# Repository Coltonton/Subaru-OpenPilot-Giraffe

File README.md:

# Subaru-OpenPilot-Giraffe(s) 

Here lies the olden and golden days of OpenPilot with Giraffes! You can use this product to interface with the CAN bus on your Subaru vehicle at EyeSight, giving the bonus ability to isolate the EyeSight module on its own separate CAN network for vehicle research, and hacking. 

Some of the Giraffes have mistakes, everything in the `/Legacy Archival Giraffes` folder is just that, a digital archive of most of my work. Most of the "development" Giraffes are lost to time and poor archival management, but live in the release of that version. DO NOT use these files as reference to build your own. ONLY use Austin, Cynthia, or Linda. 

- Intended to be used with a [Comma.ai White or Grey Panda](https://comma.ai/shop/products/panda) 

# Versions  
## -V3- 

3.0 Was the real move and evolution, finally fitting it in the cover (Also what the **Smol Bugsy Giraffe** tried to accomplish but in a different way.) I decided to stick on this path for a variety of reasons! I figured out there was no room under the cover... HOWEVER there was tons of room between the top of the EyeSight unit and the roof of the car. I already basically figured it out tho with [V1.1](#). Sometimes you have to look to the past to answer questions today! Again I was over-Zellous with V1.1; but with sure luck, the space allotted to me by the Subaru engineers was a near perfect fit for Panda... Not even a MM of clearance at the smallest point. Working even more perfectly. So is born V3! Only taking to V3 Rev 4 (NIKI) to come up with the perfect and final layout; even solving my switch problem by making the board big enough to where the switches would just be at the gap between the windshield and trim piece. giving a still invisible appearance, but not to difficult to actuate! Progress was made here!  

The V3 also brought reverse compatibility with already dead hardware (The Comma NEO) And was designed to have the factory connector pass above the EyeSight camera unit, plug into giraffe, then having a jumper connector to EyeSight. This ended up only being a possibility for the Legacy/Outback models. All other Subarus did not have the room for the chonky stock connector. Sparking V3.7+ with its Y connector to pass above the camera unit. (I still prefer the Linda design, was nicer and ALOT easier to produce....) 

### -V3.8.3 Austin- 

This is a very special edition of the Subaru Giraffe, not only is it the last version to be released; but it was sold as special edition Giraffe. Released in a special blue PCB and dedicated to the memory of my friend and classmate from grade school, Austin, who was tragically taken from us March 20th, 2019; at the too young age of 19. Until we meet again... 

This revision is still very near and dear to my heart and it pained me to no longer use it in my vehicle daily being forced to upgrade to a Black Panda, it's now on my desk where I get to see it daily. But enough with the wishy-washy crap and onto the info! As you can prolly tell by the x.x.3 i screwed this revision up.... a-couple times.... 

- The DeFacto Standard, this is what you should use! 

- Is the "gloabal platform" release Giraffe for use in all Subarus, whereas all previous V3 Giraffes were designed around a 2015 Legacy (and has a lot more room to play) 

- Replaced the 3.7 Cynthia as this version was a 3.7 special edition! But its the same thing 

### -V3.7 Cynthia- 

- First iteration of the Subaru global support 

- See [Austin](#V3.8.3-Austin) for details, they are the same, [Austin](#V3.8.3-Austin) is just a special edition of Cynthia with more beautiful routing! 

### -V3.6 Linda- 

- 2015-2019 Legacy/Outback Only 
- Added Subaru RAB Support 
- Added New Comma (Camera on CAN 3 instead of 2) Support 

### -V3.4 Niki- 

- 2015-2019 Legacy/Outback Only 
- Non RAB (Reverse Automatic Braking) Subarus ONLY 

### -V3.2 & V3.3 Gem- 

- 2015-2019 Legacy/Outback Only 
- Non RAB (Reverse Automatic Braking) Subarus ONLY 

### -V3.1 VIKI- 

- What Autum was supposed to be 

### -V3.0 Autumn- 
Dedicated to the memory of a co-worker who died unexpectedly, Autumn, to launch the 3rd generation of Subaru Giraffes (Non Working) 

## -V2- 

2.0 is a perfect example of my mind thinking more complex at first then working to simplicity. The idea with this weird Giraffe was to be like all the other Giraffes at the time where the board plugs directly into the cameras and the factory harness plugs into the board. This was a stupid idea as it would require cutting the EyeSight cover (or having it off) Witch we already had agreed was not going to happen... Too ugly, and expensive. It made a great development board as we were still trying to get the Subaru port "functional" It even uses the exact dip switches as the others. But with a twist... My overengineering mind went crazy with ideas as I knew the Giraffe would end up getting hidden up in the cover; I still wanted an easy way to have the traditional "switches" to be able to toggle Stock/Openpilot. What did I do? the only logical thing of course relays that could be hooked up to a switch and ran! It was a development platform so the *idea* was to be able to choose between dip switches or relay. I'm pretty sure they wouldn't work anyway as they are Solid state relays... idk... never tried them... 

It's funny because a year later Comma.ai made the **Subaru Access Point** with... a relay..... to control switching.... Eventually becoming the [Comma Harnes](https://comma.ai/shop/products/comma-car-harness)....  Admittedly they did do it better.... Except for using the USB Type-C Connectors...... It would of been the eventual evolution of my product to go back to relay control anyway! I take one big leap, have to crawl backwards crying and work my way back.....   

## -V1- 

Mr Overthinkers, first Giraffe overthink, before I found out Panda did fit somewhere in the EyeSight cover I had the brilliant idea to tear apart the Comma Panda and just put it on the Giraffe 

Rip White Panda - unknown year 

Features Eletronic relays that could be used to solve our switch situation (im writing this in reverse order so see V2 for info on that....) 

## -V0.1- 

**My First PCB** features include: 
- 90deg track corners 
- Weird angle lines (non 45deg multiple) 
- OBD socket doesn't even fit 
- Eyesight connectors don't even fit 
- No idea what I was doing (clearly) 
- Absolute trash 
- Prolly will blow up your car

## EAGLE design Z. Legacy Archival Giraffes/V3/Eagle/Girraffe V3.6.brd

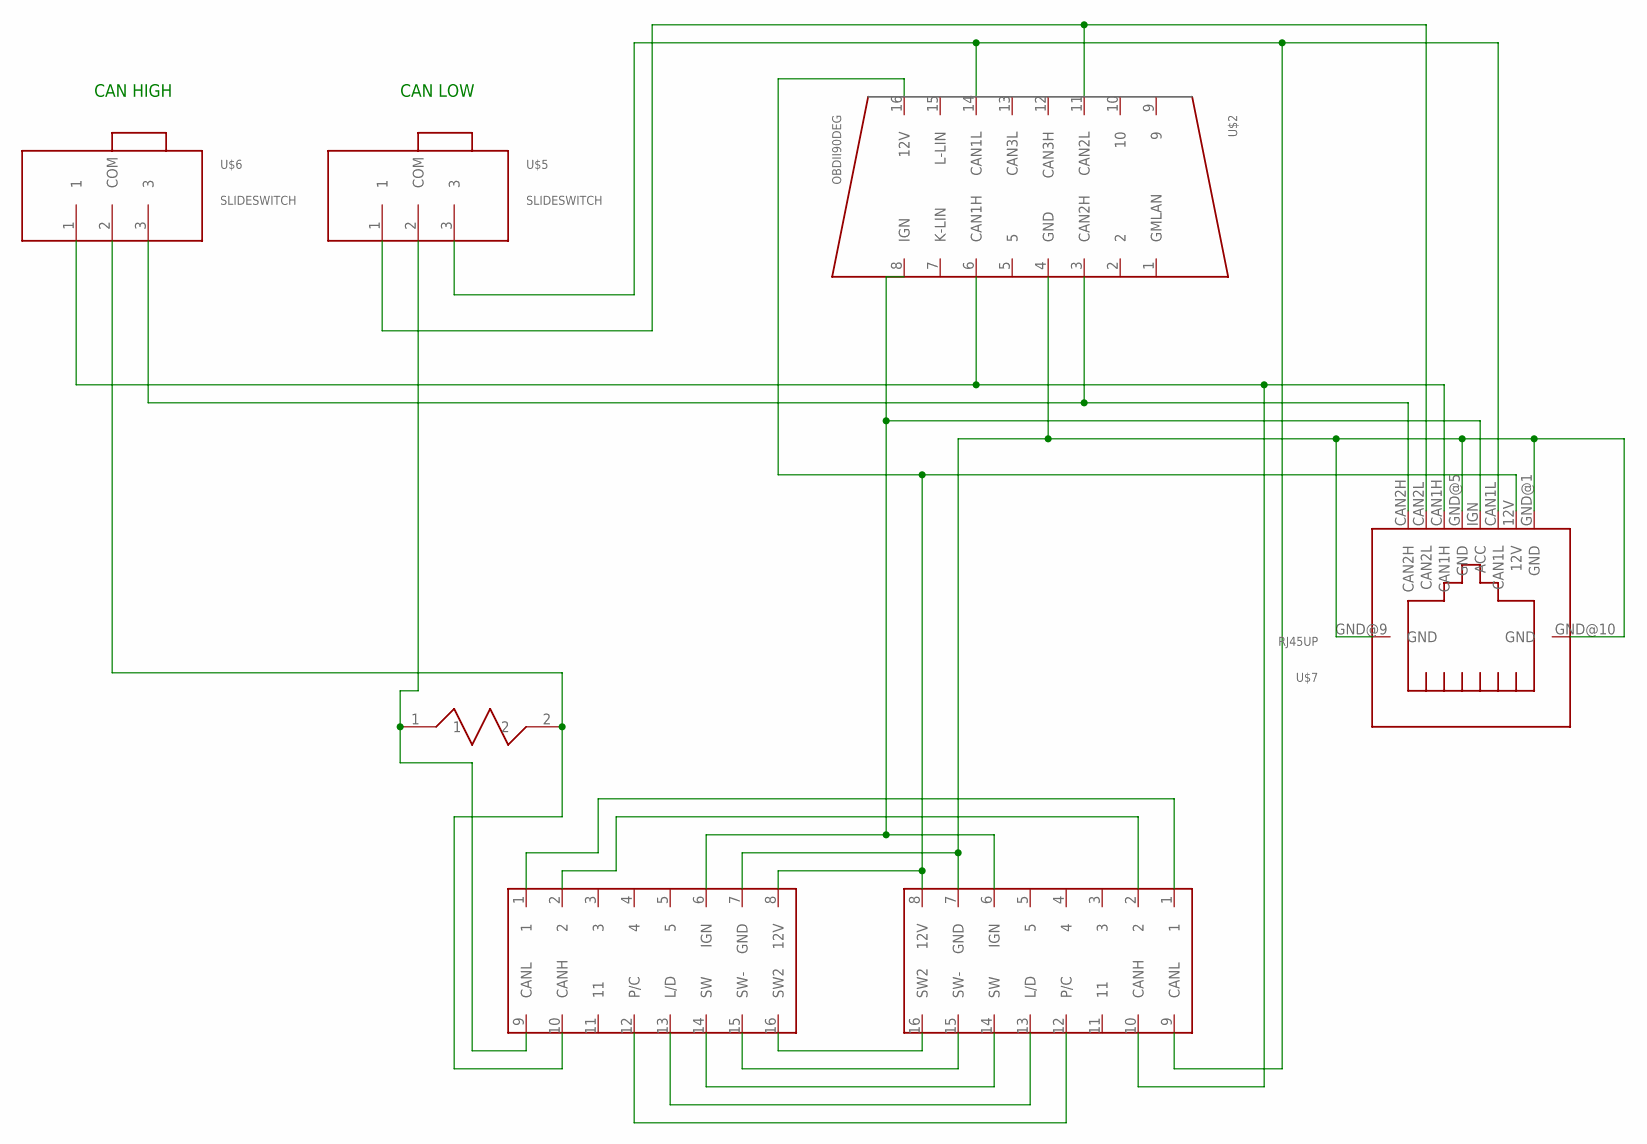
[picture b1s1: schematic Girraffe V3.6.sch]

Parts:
U$1: 120OHM
U$2: OBDII90DEG; OBDII
U$3: R137IN; R137
U$4: R137OUT
U$5, U$6: SLIDESWITCH
U$7: RJ45UP; VERRJ45

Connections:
12V: U$2.16 (12V), U$3.8 (12V), U$4.8 (12V), U$7.12V
ACC: U$2.8 (IGN), U$3.6 (IGN), U$4.6 (IGN), U$7.IGN (ACC)
GND: U$2.4 (GND), U$3.7 (GND), U$4.7 (GND), U$7.GND@1 (GND), U$7.GND@5 (GND), U$7.GND@9 (GND), U$7.GND@10 (GND)
unnamed: U$1.1, U$4.9 (CANL), U$5.2 (COM)
unnamed: U$1.2, U$4.10 (CANH), U$6.2 (COM)
unnamed: U$2.14 (CAN1L), U$3.9 (CANL), U$5.3, U$7.CAN1L
unnamed: U$2.11 (CAN2L), U$5.1, U$7.CAN2L
unnamed: U$2.6 (CAN1H), U$3.10 (CANH), U$6.1, U$7.CAN1H
unnamed: U$2.3 (CAN2H), U$6.3, U$7.CAN2H
unnamed: U$3.16 (SW2), U$4.16 (SW2)
unnamed: U$3.15 (SW-), U$4.15 (SW-)
unnamed: U$3.14 (SW), U$4.14 (SW)
unnamed: U$3.13 (L/D), U$4.13 (L/D)
unnamed: U$3.12 (P/C), U$4.12 (P/C)
unnamed: U$3.2, U$4.2
unnamed: U$3.1, U$4.1

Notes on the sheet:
CAN LOW
CAN HIGH

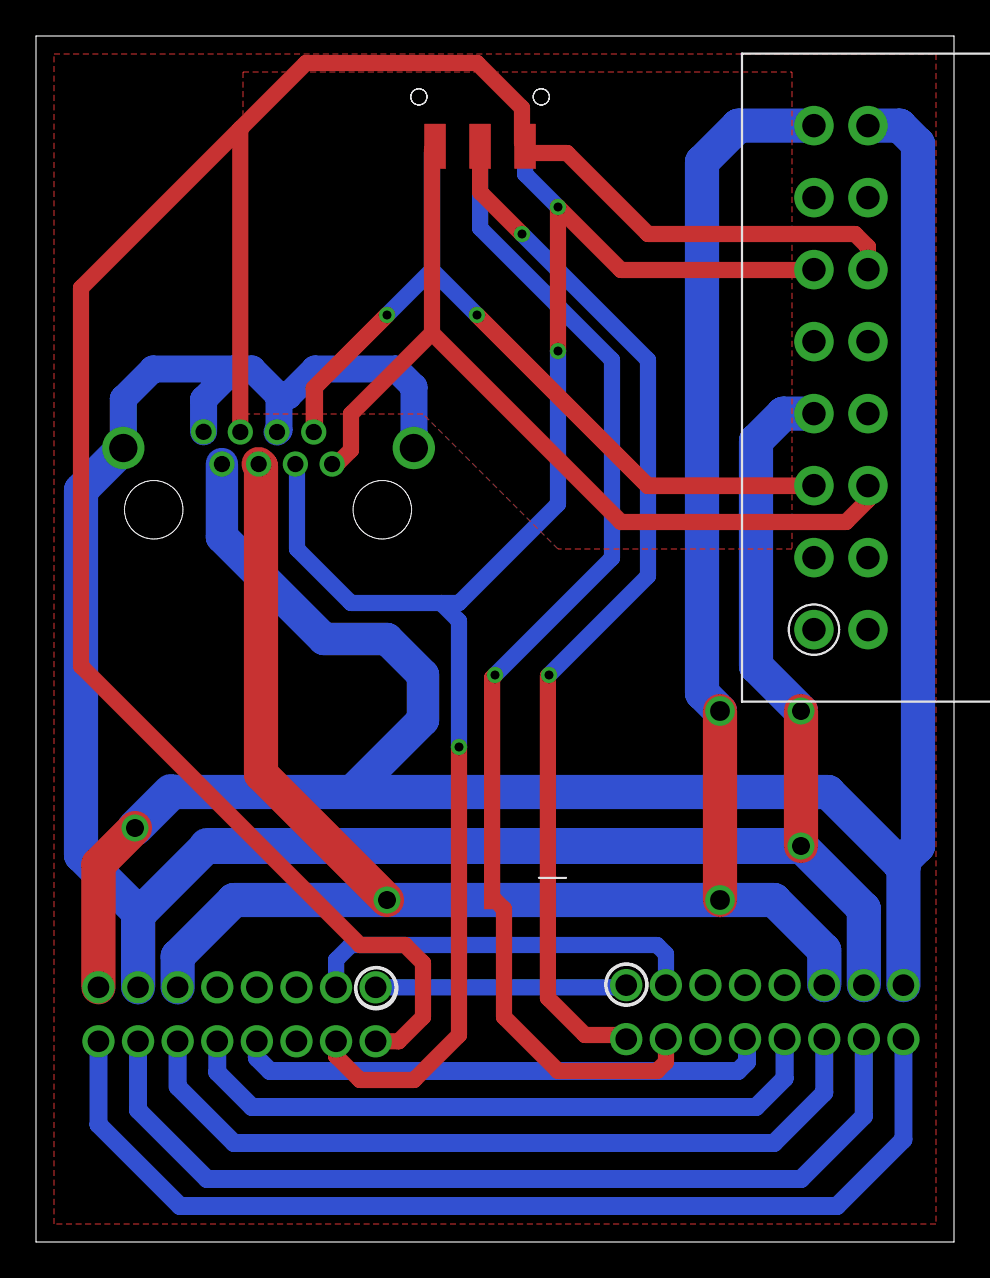
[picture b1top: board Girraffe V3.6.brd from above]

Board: 2 copper layers, 51.0 x 67.0 mm, 7 parts (1 on the bottom side), 16 nets.

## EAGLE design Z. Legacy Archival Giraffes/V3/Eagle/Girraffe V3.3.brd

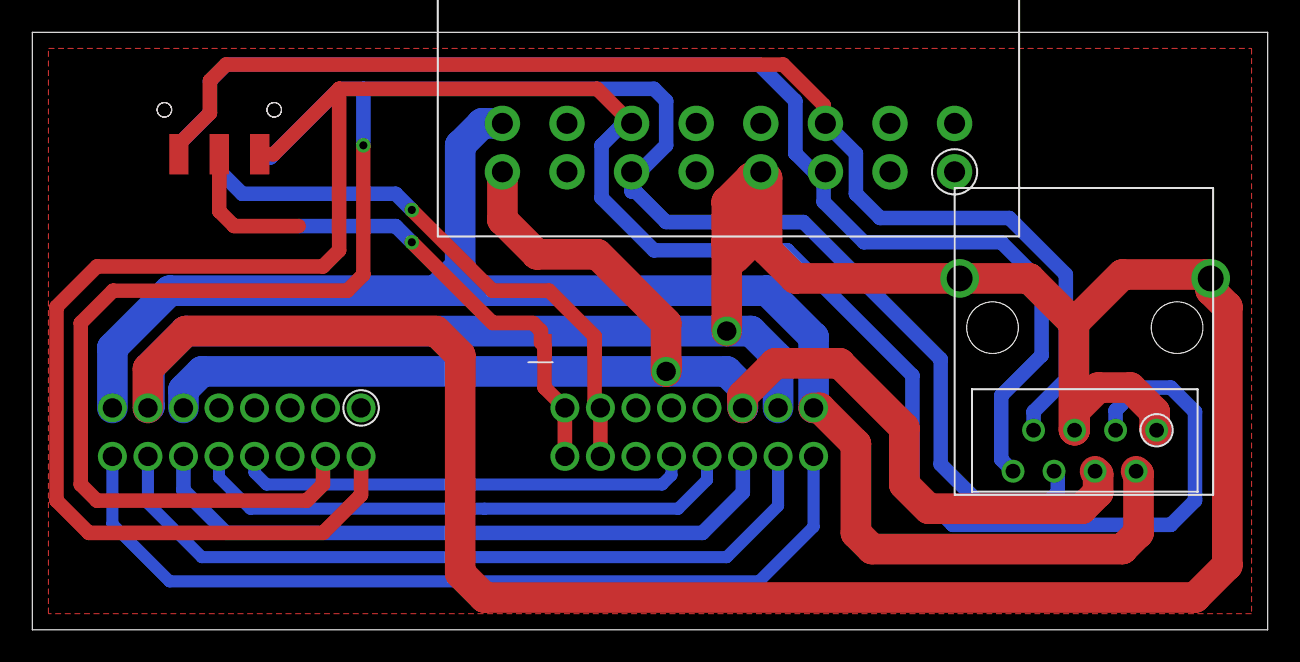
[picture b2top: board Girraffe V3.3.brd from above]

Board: 2 copper layers, 76.5 x 37.0 mm, 7 parts (1 on the bottom side), 14 nets.

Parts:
U$1: 120OHM
U$2: OBDII90DEG; OBDII
U$3: R137IN; R137
U$4: R137OUT
U$5, U$6: SLIDESWITCH
U$8: RJ45

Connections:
12V: U$2.16, U$3.8, U$4.8, U$8.12V
ACC: U$2.8, U$3.6, U$4.6, U$8.IGN
GND: U$2.4, U$3.7, U$4.7, U$8.GND@1, U$8.GND@5, U$8.GND@9, U$8.GND@10
unnamed: U$1.1, U$4.1, U$4.9, U$5.2
unnamed: U$1.2, U$4.2, U$4.10, U$6.2
unnamed: U$2.14, U$3.9, U$5.3, U$8.CAN1L
unnamed: U$2.11, U$5.1, U$8.CAN2L
unnamed: U$2.6, U$3.10, U$6.1, U$8.CAN1H
unnamed: U$2.3, U$6.3, U$8.CAN2H
unnamed: U$3.16, U$4.16
unnamed: U$3.15, U$4.15
unnamed: U$3.14, U$4.14
unnamed: U$3.13, U$4.13
unnamed: U$3.12, U$4.12

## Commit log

2021-05-12 Initial Upload of Files
2021-05-14 Updates for Readme and File Struct
2021-05-17 preview edits
2021-05-17 Upload Photos
2021-05-17 FInal Readme updates for now + list of words I cant spell
2021-05-17 License update, list of words I cant spell
